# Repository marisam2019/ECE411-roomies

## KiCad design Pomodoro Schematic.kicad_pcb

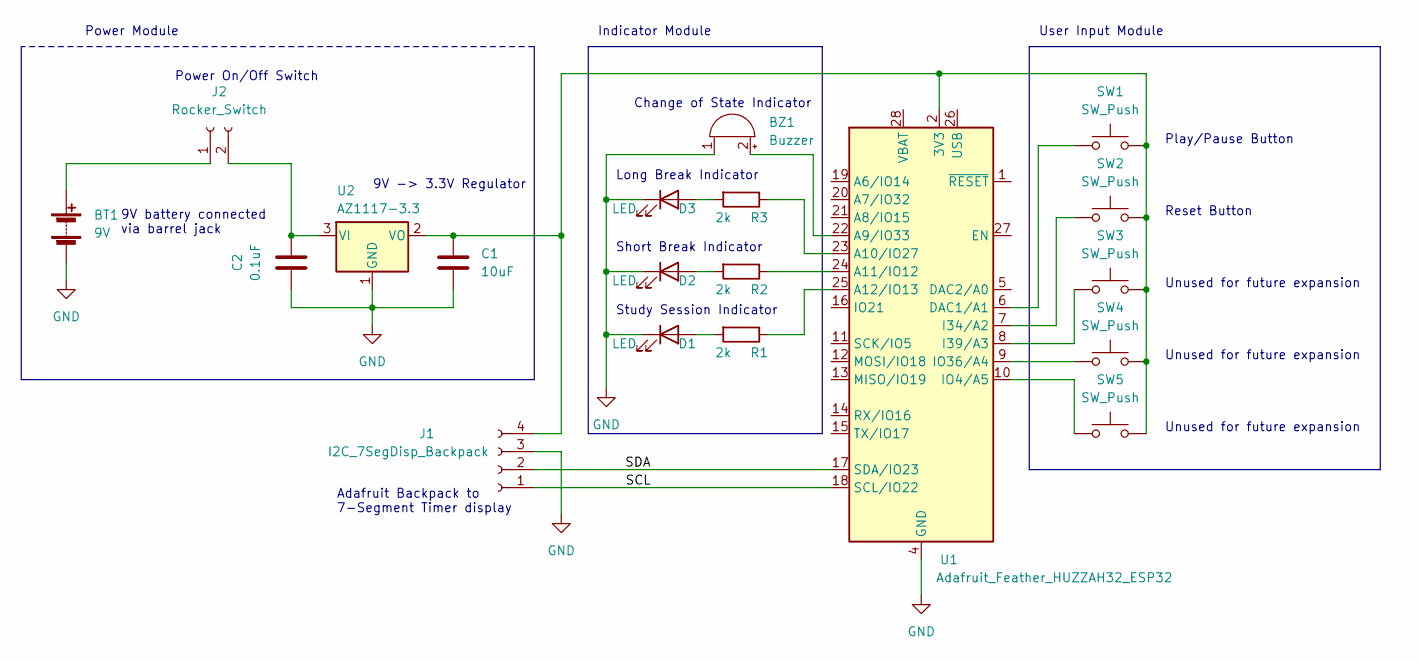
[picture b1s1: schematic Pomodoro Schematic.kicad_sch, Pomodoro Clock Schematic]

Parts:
BT1: 9V; BarrelJack_CUI_PJ-102AH_Horizontal
BZ1: Buzzer; Buzzer_12x9.5RM7.6
C1: 10uF; CP_Radial_D8.0mm_P3.50mm
C2: 0.1uF; C_0603_1608Metric
D1, D2, D3: LED; LED_D3.0mm
J1: I2C_7SegDisp_Backpack; PinHeader_1x04_P2.54mm_Vertical
J2: Rocker_Switch; PinHeader_1x02_P2.54mm_Vertical
R1, R2, R3: 2k; R_Axial_DIN0204_L3.6mm_D1.6mm_P7.62mm_Horizontal
SW1, SW2, SW3, SW4, SW5: SW_Push; SW_PUSH_6mm
U1: Adafruit_Feather_HUZZAH32_ESP32; Adafruit_Feather
U2: AZ1117-3.3; SOT-223

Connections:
/SCL: J1.1, U1.18 (SCL/IO22)
/SDA: J1.2, U1.17 (SDA/IO23)
GND: BT1.2 (-), BZ1.1 (-), C1.2, C2.1, D1.1 (K), D2.1 (K), D3.1 (K), J1.3, U1.4 (GND), U2.1 (GND)
unnamed: C2.2, J2.2, U2.3 (VI)
unnamed: D1.2 (A), R1.2
unnamed: D2.2 (A), R2.2
unnamed: D3.2 (A), R3.2
unnamed: BT1.1 (+), J2.1
unnamed: R2.1, U1.24 (A11/IO12)
unnamed: C1.1, J1.4, SW1.2, SW2.2, SW3.2, SW4.2, SW5.2, U1.2 (3V3), U2.2 (VO)
unnamed: SW1.1, U1.6 (DAC1/A1)
unnamed: SW2.1, U1.7 (I34/A2)
unnamed: SW3.1, U1.8 (I39/A3)
unnamed: SW4.1, U1.9 (IO36/A4)
unnamed: SW5.1, U1.10 (IO4/A5)
unnamed: BZ1.2 (+), U1.22 (A9/IO33)
unnamed: R3.1, U1.23 (A10/IO27)
unnamed: R1.1, U1.25 (A12/IO13)

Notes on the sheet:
Unused for future expansion
9V battery connected via barrel jack
Adafruit Backpack to 7-Segment Timer display
Long Break Indicator
Study Session Indicator
Power Module
Indicator Module
User Input Module
Play/Pause Button
Reset Button
Short Break Indicator
Power On/Off Switch
9V -> 3.3V Regulator
Change of State Indicator

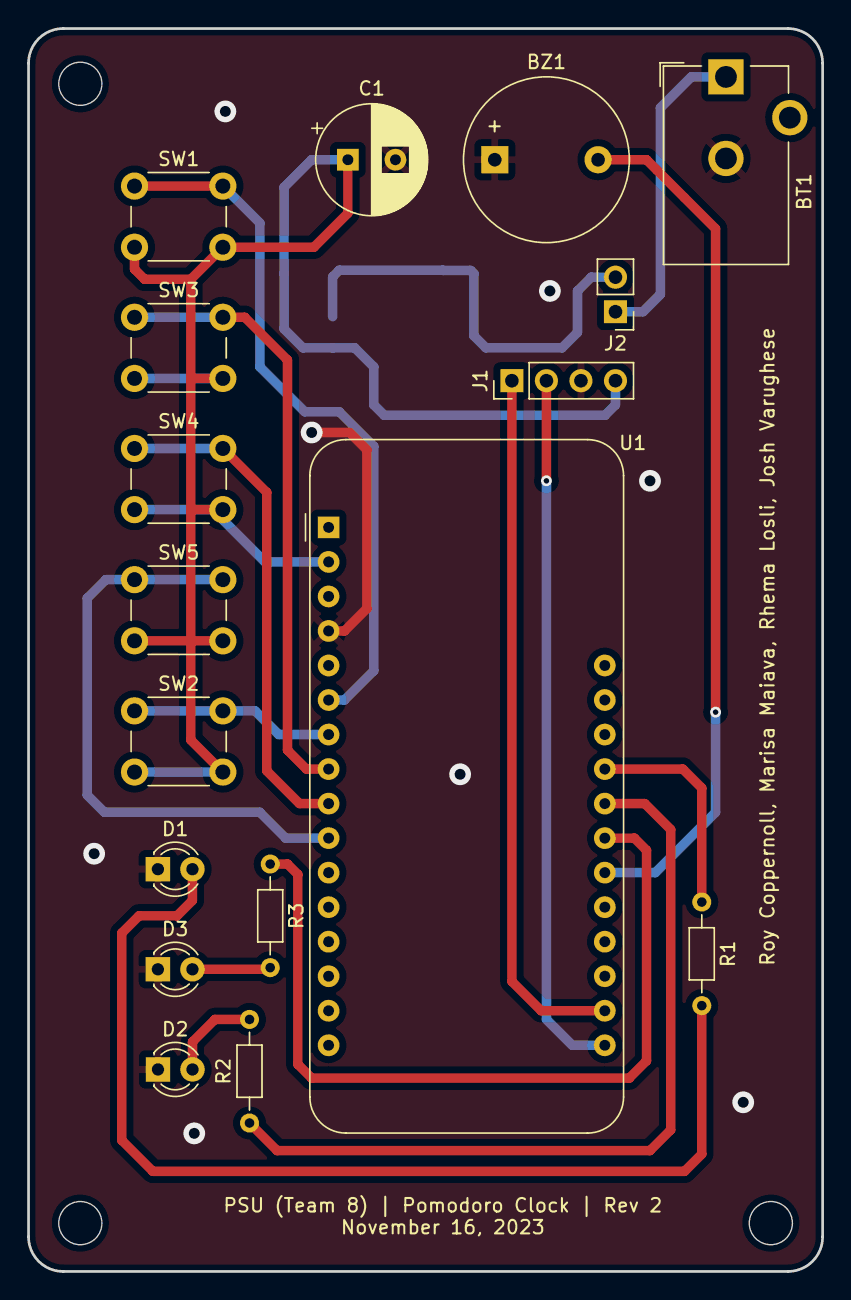
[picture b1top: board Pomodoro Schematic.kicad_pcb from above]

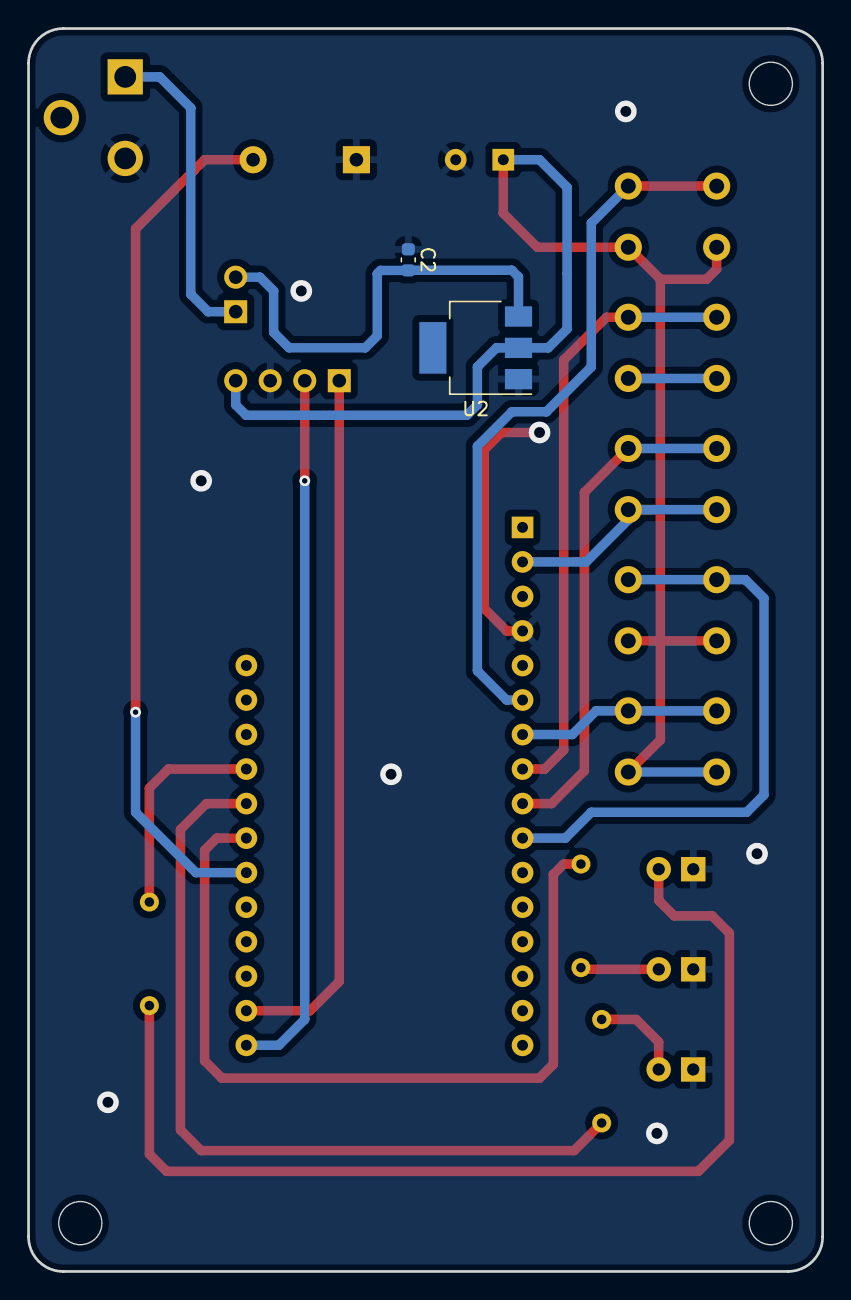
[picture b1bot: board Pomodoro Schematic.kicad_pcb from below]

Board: 2 copper layers, 58.4 x 91.4 mm, 19 parts (2 on the bottom side), 18 nets.

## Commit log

2023-11-02 Add files via upload
    Status Report:
    Team 8 is waiting on the multiplexer for the 7-segment display to arrive. Once that gets here, we can create the countdown timer. In the meantime, we will write pseudo-code for the entire project and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
2023-11-08 Add files via upload
    Voltage divider that takes 9V input and delivers 3.29V output. A non-inverting op-amp with unity gain is added so that the load resistance does not effect the voltage divider.
2023-12-02 Add files via upload
    test arduino code to test functionality of the LEDs, buttons, and 7-segment display.
2023-12-06 Add files via upload
    Updated code as Dec 5. Attempts to incorporate functions to implement the timer modes. Currently goes through only the first function and then displays --.-- on the display.
2023-12-06 Add files via upload
    goes to each state counter and then returns to the main loop
2023-12-06 Add files via upload
    passes state timing information to one "countdown" function instead of one function for each state
2023-12-07 Team 8 - Test Plans (Test Case and Matrix Test
2023-12-07 Update WORKING_CODE.ino
    Changed program to use accurate timing (i.e 25 min, 5 min, 30 min for focus, short_break, long_break respectively).
